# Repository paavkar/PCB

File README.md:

# PCB projects

## Introduction

This repository is meant for my PCB projects.

## IoT-Device

This is a PCB project where I am trying to design my own IoT device.
The MCU used in this is STM32U585VI with a ESP32-C3-WROOM-02 as a WiFi co-processor.
The design includes a reset-boot logic to choose the boot mode (i.e. either to
bootloader or flash). Included is also a port for SWD. In this board, USB-C is
used in 2.0 speed to give the board power and program the board.

### Schematic

You can take a look at the schematic in this repo from this
<a href="/IoT-Device/schematic.pdf">link.</a>

## Metro-M4-Express-Shield

This project is a much more simpler one as it is only a shield for the Metro M4 Express.
The goal of this PCB project was to design a shield that adds WiFi functionality
to the development board. The WiFi-module used is the ESP32-WROOM-32E, which is
used as a base for the FireBeetle board.

### Schematic

The schematic is available on this repo from the following
<a href="/Metro-M4-Express-Shield/schematics/schematic.pdf">link.</a>

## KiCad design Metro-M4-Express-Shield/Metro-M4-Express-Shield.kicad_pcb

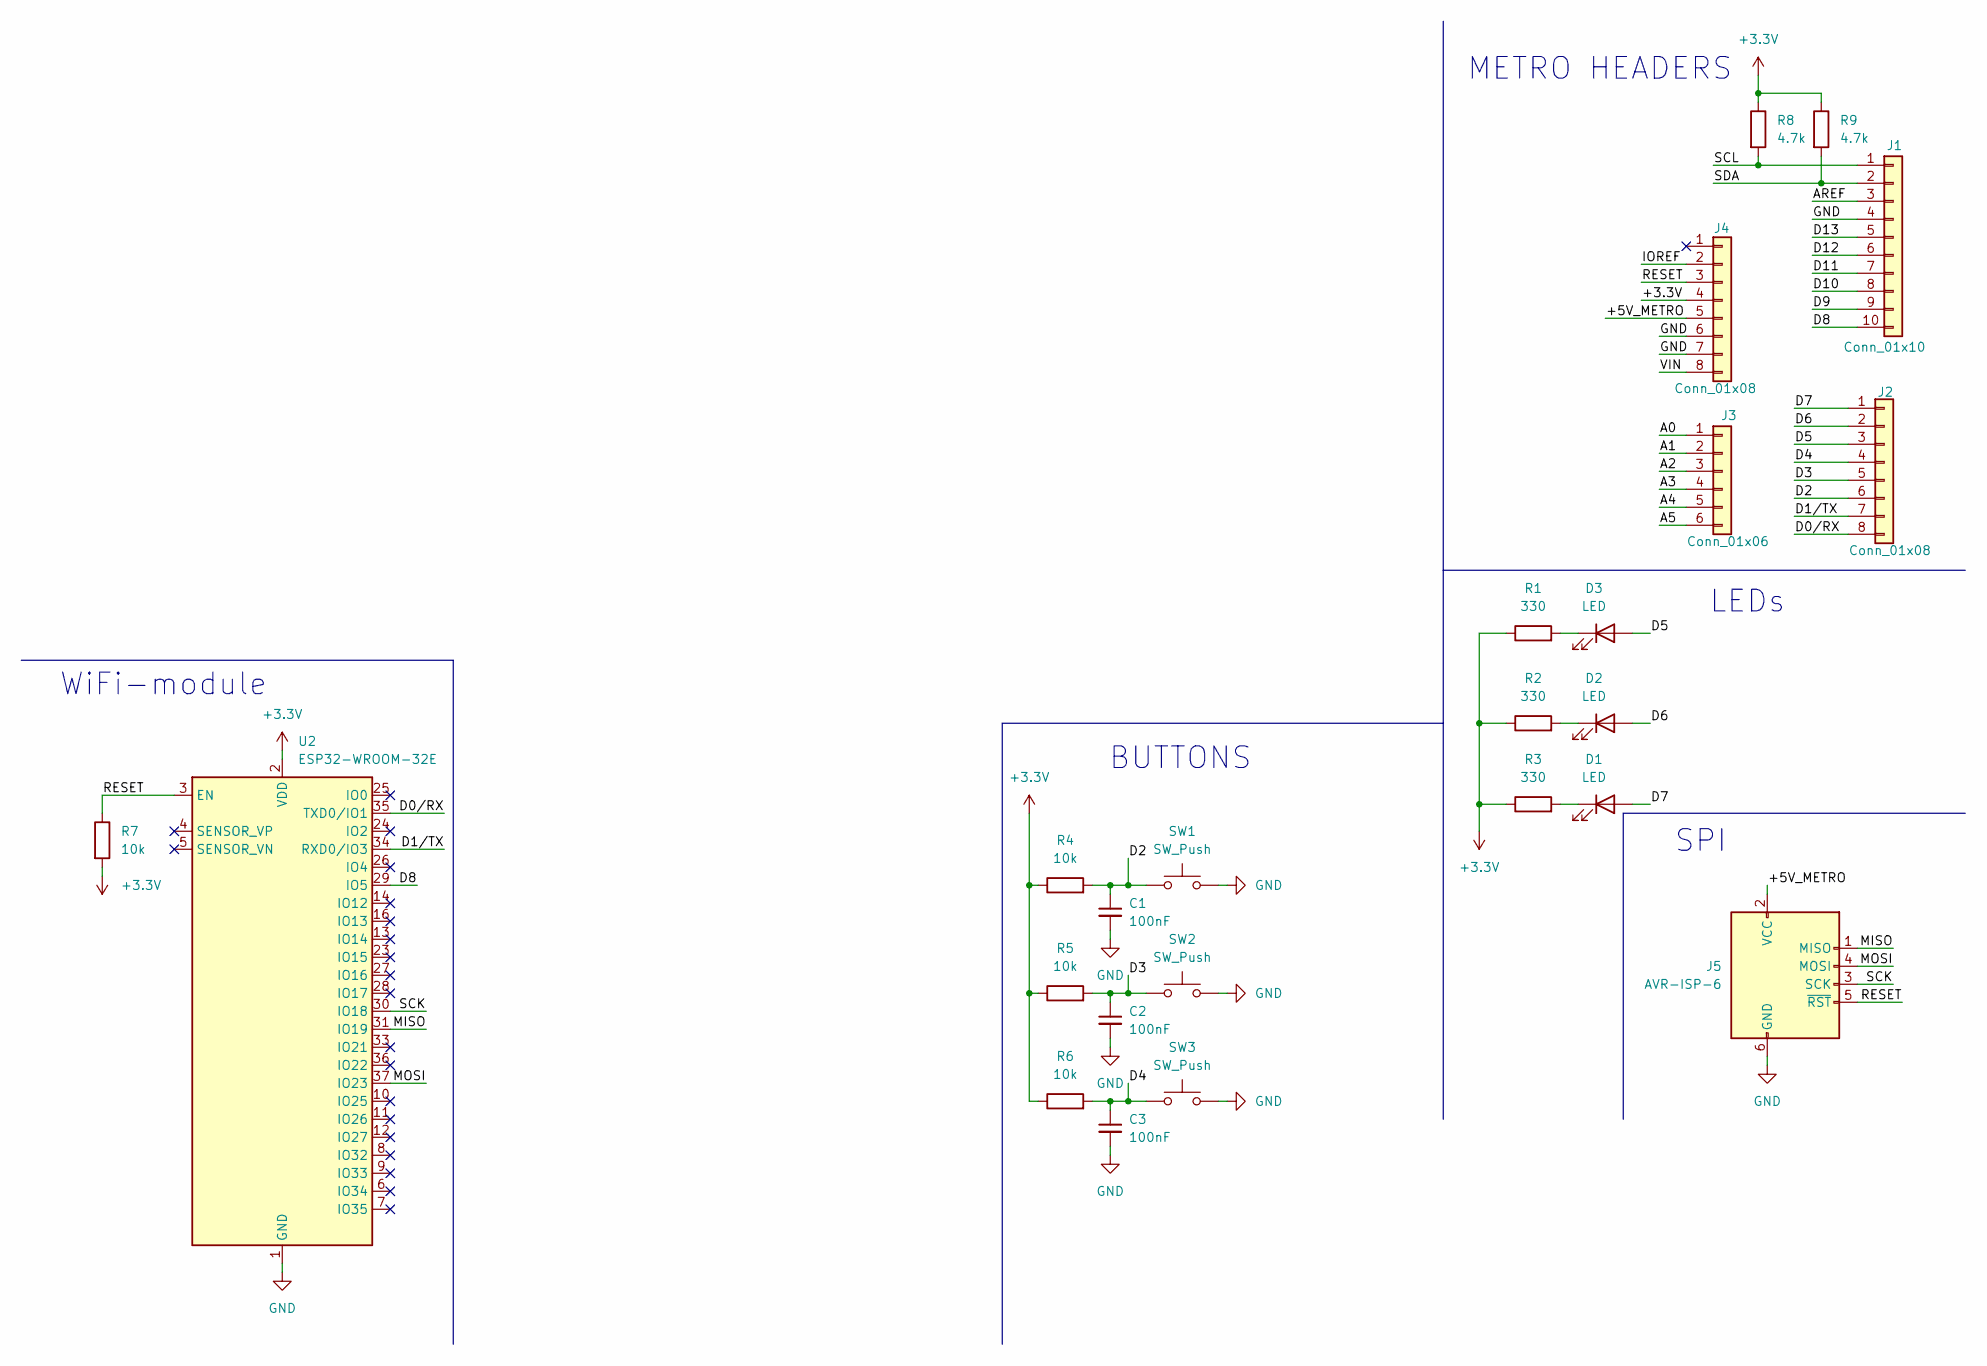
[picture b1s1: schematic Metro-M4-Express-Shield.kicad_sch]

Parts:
C1, C2, C3: 100nF; C_0603_1608Metric
D1, D2, D3: LED; LED_0603_1608Metric
J1: Conn_01x10; PinHeader_1x10_P2.54mm_Vertical
J2, J4: Conn_01x08; PinHeader_1x08_P2.54mm_Vertical
J3: Conn_01x06; PinHeader_1x06_P2.54mm_Vertical
J5: AVR-ISP-6; PinSocket_2x03_P2.54mm_Vertical
R1, R2, R3: 330; R_0603_1608Metric
R4, R5, R6, R7: 10k; R_0603_1608Metric
R8, R9: 4.7k; R_0603_1608Metric
SW1, SW2, SW3: SW_Push; SW_SPST_PTS647_Sx50
U2: ESP32-WROOM-32E; ESP32-WROOM-32D

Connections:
+3.3V: J4.4, R1.1, R2.1, R3.1, R4.1, R5.1, R6.1, R7.2, R8.1, R9.1, U2.2 (VDD)
/+5V_METRO: J4.5, J5.2 (VCC)
/A0: J3.1
/A1: J3.2
/A2: J3.3
/A3: J3.4
/A4: J3.5
/A5: J3.6
/AREF: J1.3
/D0/RX: J2.8, U2.35 (TXD0/IO1)
/D1/TX: J2.7, U2.34 (RXD0/IO3)
/D2: C1.1, J2.6, R4.2, SW1.1
/D3: C2.1, J2.5, R5.2, SW2.1
/D4: C3.1, J2.4, R6.2, SW3.1
/D5: D3.2 (A), J2.3
/D6: D2.2 (A), J2.2
/D7: D1.2 (A), J2.1
/D8: J1.10, U2.29 (IO5)
/D9: J1.9
/D10: J1.8
/D11: J1.7
/D12: J1.6
/D13: J1.5
/IOREF: J4.2
/MISO: J5.1 (MISO), U2.31 (IO19)
/MOSI: J5.4 (MOSI), U2.37 (IO23)
/RESET: J4.3, J5.5 (~RST), R7.1, U2.3 (EN)
/SCK: J5.3 (SCK), U2.30 (IO18)
/SCL: J1.1, R8.2
/SDA: J1.2, R9.2
/VIN: J4.8
GND: C1.2, C2.2, C3.2, J1.4, J4.6, J4.7, J5.6 (GND), SW1.2, SW2.2, SW3.2, U2.1 (GND), U2.15 (GND), U2.38 (GND), U2.39 (GND)
unnamed: D1.1 (K), R3.2
unnamed: D2.1 (K), R2.2
unnamed: D3.1 (K), R1.2

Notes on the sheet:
SPI
METRO HEADERS
WiFi-module
LEDs
BUTTONS

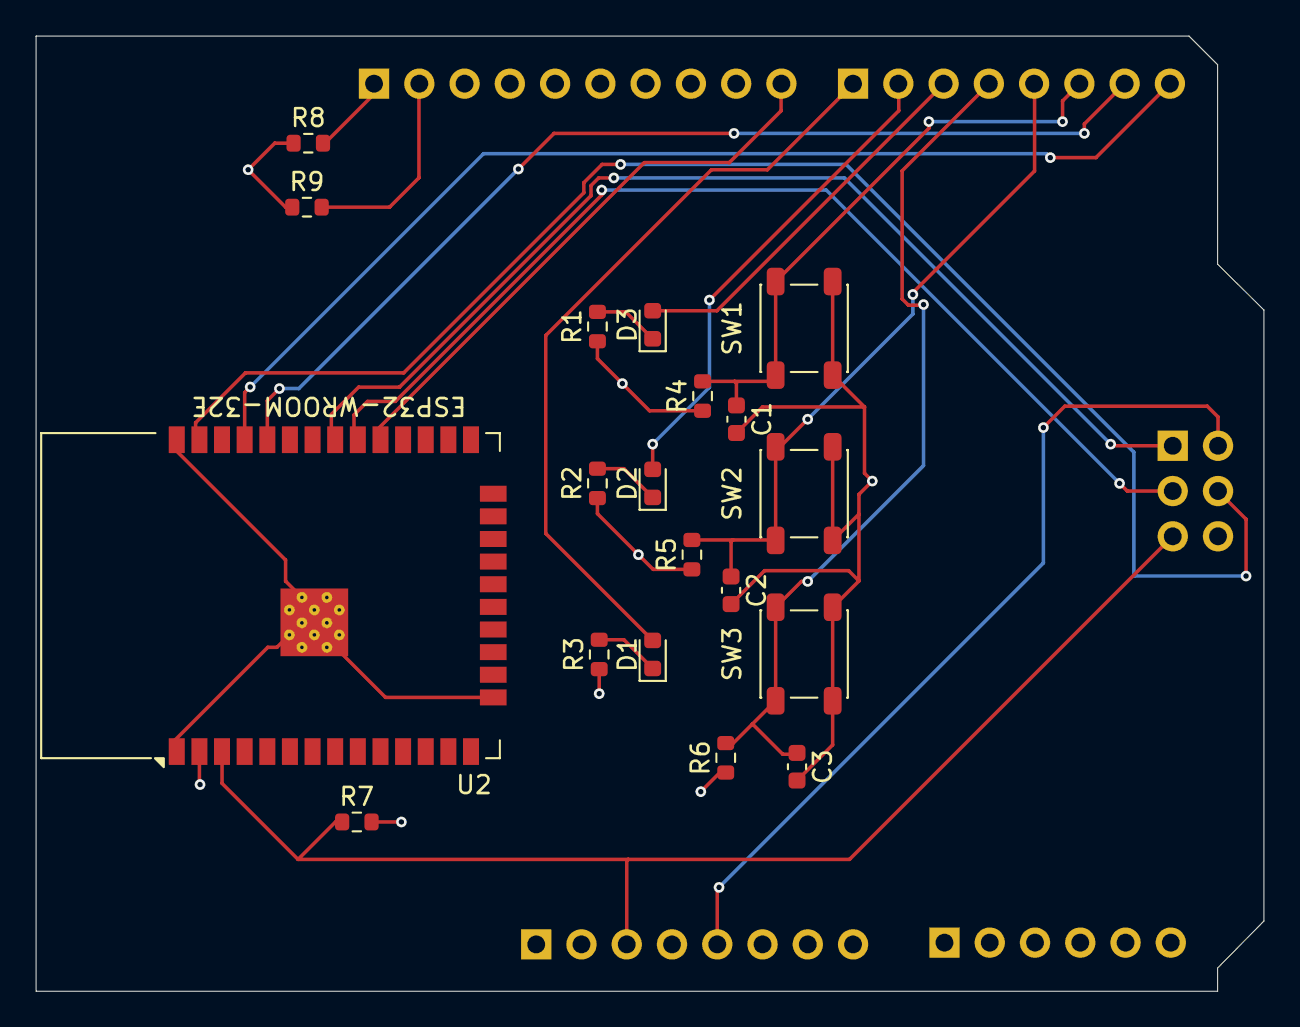
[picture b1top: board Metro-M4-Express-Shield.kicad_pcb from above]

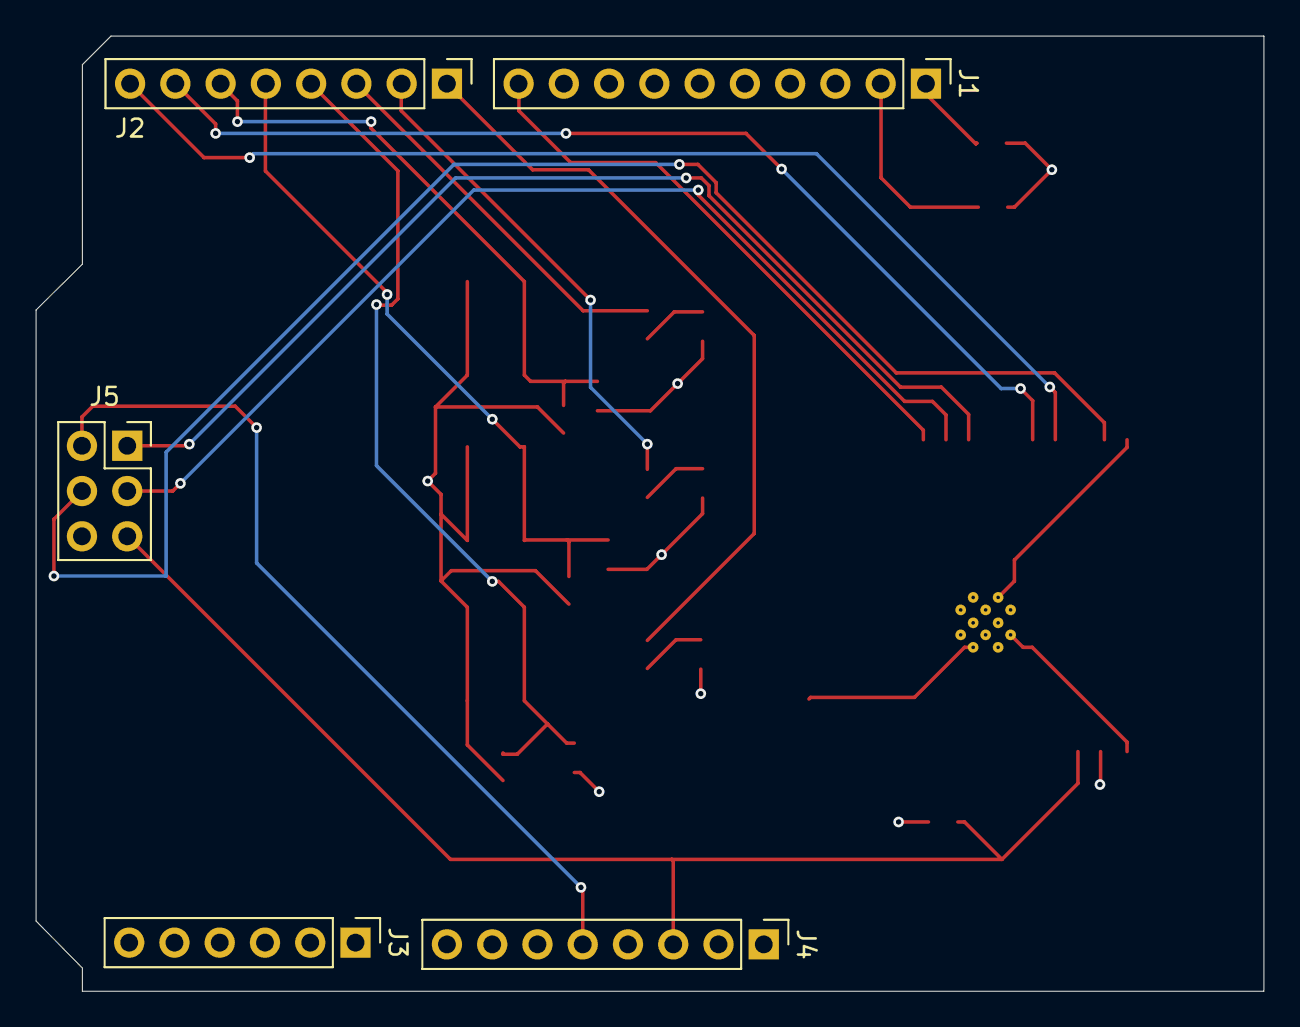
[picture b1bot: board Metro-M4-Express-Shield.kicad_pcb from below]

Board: 4 copper layers, 68.9 x 53.6 mm, 24 parts (5 on the bottom side), 21 nets.

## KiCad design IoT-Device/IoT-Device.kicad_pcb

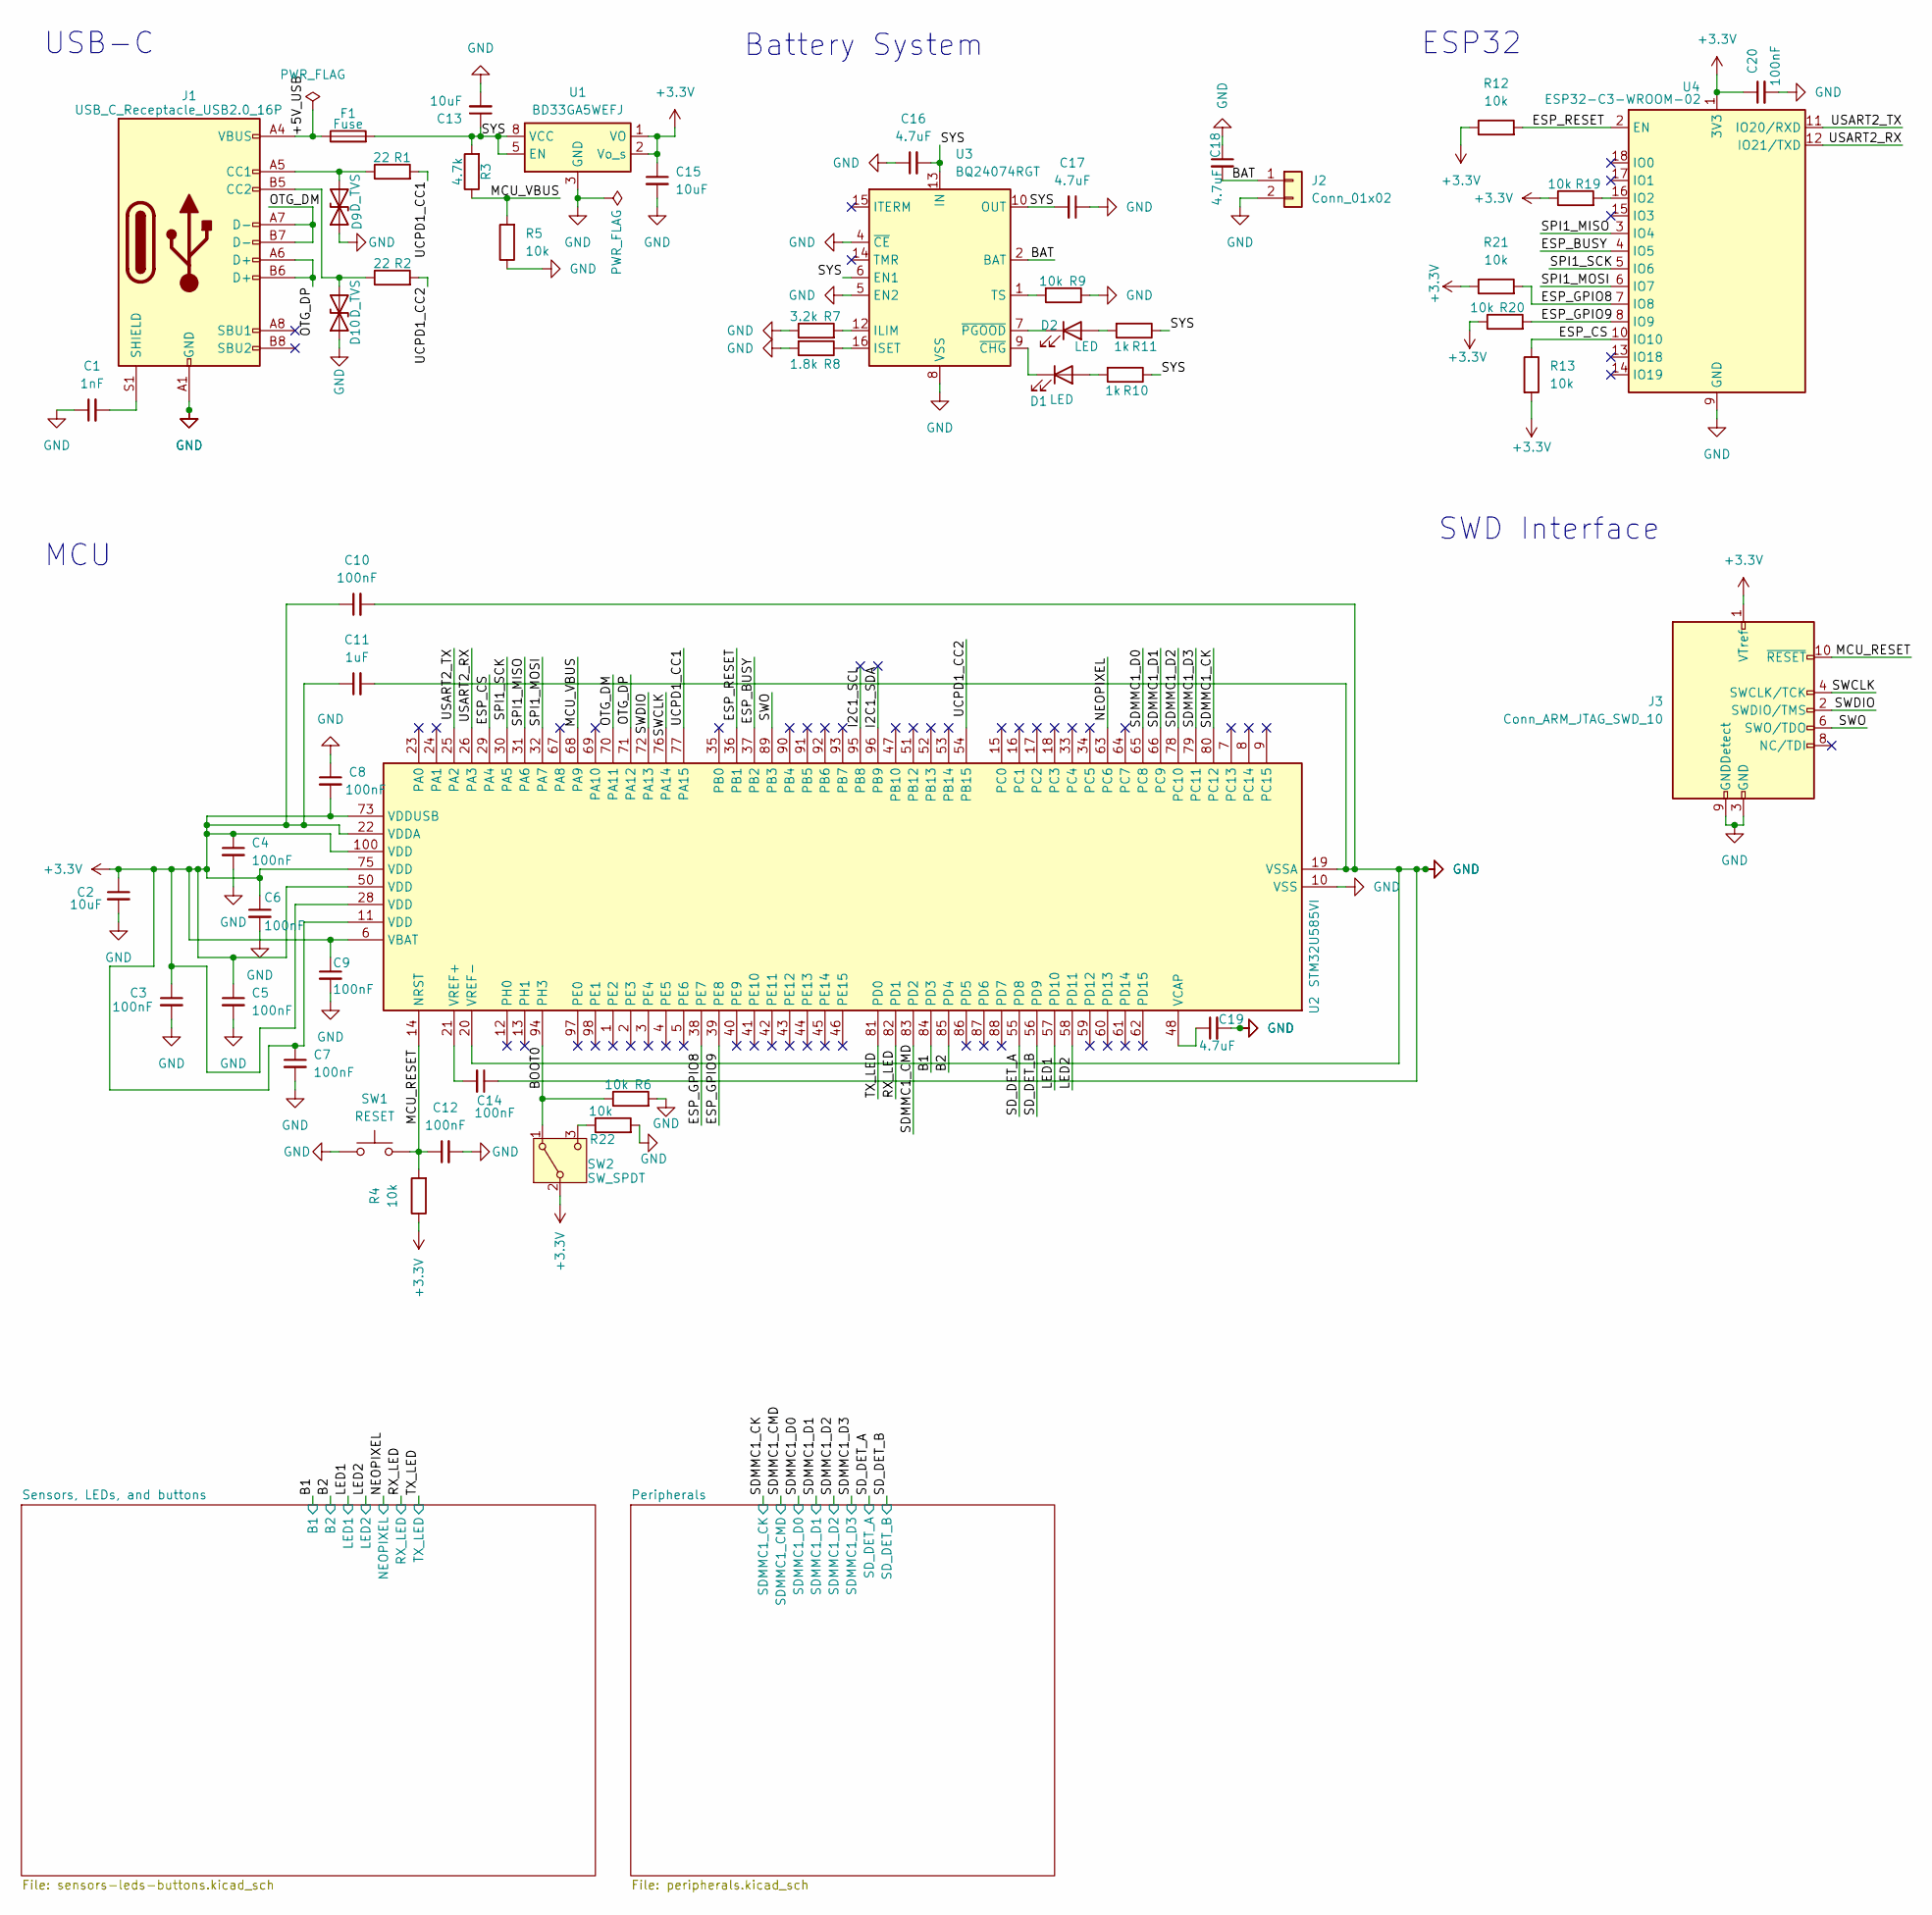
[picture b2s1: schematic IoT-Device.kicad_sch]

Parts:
C1: 1nF; C_0603_1608Metric
C2, C13, C15: 10uF; C_0603_1608Metric
C3, C4, C5, C6, C7, C8, C9, C10, C12, C14, C20: 100nF; C_0603_1608Metric
C11: 1uF; C_0603_1608Metric
C16, C17, C18, C19: 4.7uF; C_0603_1608Metric
D1, D2: LED; LED_0603_1608Metric
D9, D10: D_TVS; D_0603_1608Metric
F1: Fuse; Fuse_0603_1608Metric
J1: USB_C_Receptacle_USB2.0_16P; USB_C_Receptacle_GCT_USB4105-xx-A_16P_TopMnt_Horizontal
J2: Conn_01x02; JST_PH_B2B-PH-K_1x02_P2.00mm_Vertical
J3: Conn_ARM_JTAG_SWD_10; PinHeader_2x05_P1.27mm_Vertical_SMD
R1, R2: 22; R_0603_1608Metric
R3: 4.7k; R_0603_1608Metric
R4, R5, R6, R9, R12, R13, R19, R20, R21, R22: 10k; R_0603_1608Metric
R7: 3.2k; R_0603_1608Metric
R8: 1.8k; R_0603_1608Metric
R10, R11: 1k; R_0603_1608Metric
SW1: RESET; SW_SPST_PTS647_Sx50
SW2: SW_SPDT; SW_SPDT_PCM12
U1: BD33GA5WEFJ; HTSOP-8-1EP_3.9x4.9mm_P1.27mm_EP2.4x3.2mm
U2: STM32U585VI; LQFP-100_14x14mm_P0.5mm
U3: BQ24074RGT; VQFN-16-1EP_3x3mm_P0.5mm_EP1.6x1.6mm
U4: ESP32-C3-WROOM-02

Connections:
/+5V_USB: F1.1, J1.A4 (VBUS), J1.A9 (VBUS), J1.B4 (VBUS), J1.B9 (VBUS)
/B1: U2.84 (PD3); also elsewhere on the board
/B2: U2.85 (PD4); also elsewhere on the board
/BAT: C18.2, J2.1, U3.2 (BAT), U3.3 (BAT)
/BOOT0: R6.1, SW2.1 (A), U2.94 (PH3)
/ESP_BUSY: U2.37 (PB2), U4.4 (IO5)
/ESP_CS: R13.1, U2.29 (PA4), U4.10 (IO10)
/ESP_GPIO8: R21.2, U2.38 (PE7), U4.7 (IO8)
/ESP_GPIO9: R20.2, U2.39 (PE8), U4.8 (IO9)
/ESP_RESET: R12.2, U2.36 (PB1), U4.2 (EN)
/I2C1_SCL: U2.95 (PB8)
/I2C1_SDA: U2.96 (PB9)
/LED1: U2.57 (PD10); also elsewhere on the board
/LED2: U2.58 (PD11); also elsewhere on the board
/MCU_RESET: C12.1, J3.10 (~RESET), R4.2, SW1.2, U2.14 (NRST)
/MCU_VBUS: R3.1, R5.2, U2.68 (PA9)
/NEOPIXEL: U2.63 (PC6); also elsewhere on the board
/OTG_DM: J1.A7 (D-), J1.B7 (D-), U2.70 (PA11)
/OTG_DP: J1.A6 (D+), J1.B6 (D+), U2.71 (PA12)
/RX_LED: U2.82 (PD1); also elsewhere on the board
/SDMMC1_CK: U2.80 (PC12); also elsewhere on the board
/SDMMC1_CMD: U2.83 (PD2); also elsewhere on the board
/SDMMC1_D0: U2.65 (PC8); also elsewhere on the board
/SDMMC1_D1: U2.66 (PC9); also elsewhere on the board
/SDMMC1_D2: U2.78 (PC10); also elsewhere on the board
/SDMMC1_D3: U2.79 (PC11); also elsewhere on the board
/SD_DET_A: U2.55 (PD8); also elsewhere on the board
/SD_DET_B: U2.56 (PD9); also elsewhere on the board
/SPI1_MISO: U2.31 (PA6), U4.3 (IO4)
/SPI1_MOSI: U2.32 (PA7), U4.6 (IO7)
/SPI1_SCK: U2.30 (PA5), U4.5 (IO6)
/SWCLK: J3.4 (SWCLK/TCK), U2.76 (PA14)
/SWDIO: J3.2 (SWDIO/TMS), U2.72 (PA13)
/SWO: J3.6 (SWO/TDO), U2.89 (PB3)
/SYS: C13.1, C16.2, C17.2, F1.2, R3.2, R10.1, R11.1, U1.5 (EN), U1.8 (VCC), U3.6 (EN1), U3.10 (OUT), U3.11 (OUT), U3.13 (IN)
/TX_LED: U2.81 (PD0); also elsewhere on the board
/UCPD1_CC1: R1.2, U2.77 (PA15)
/UCPD1_CC2: R2.2, U2.54 (PB15)
/USART2_RX: U2.26 (PA3), U4.12 (IO21/TXD)
/USART2_TX: U2.25 (PA2), U4.11 (IO20/RXD)
unnamed: D1.2 (A), R10.2
unnamed: D1.1 (K), U3.9 (~CHG)
unnamed: D2.2 (A), R11.2
unnamed: D2.1 (K), U3.7 (~PGOOD)
unnamed: D9.2 (A2), J1.A5 (CC1), R1.1
unnamed: D10.2 (A2), J1.B5 (CC2), R2.1
unnamed: C1.2, J1.S1 (SHIELD)
unnamed: R22.1, SW2.3 (C)
unnamed: C19.1, U2.48 (VCAP)
unnamed: C14.2, U2.21 (VREF+)
unnamed: R7.2, U3.12 (ILIM)
unnamed: R8.1, U3.16 (ISET)
unnamed: R9.2, U3.1 (TS)
unnamed: R19.2, U4.16 (IO2)

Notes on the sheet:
SWD Interface
Battery System
MCU
ESP32
USB-C

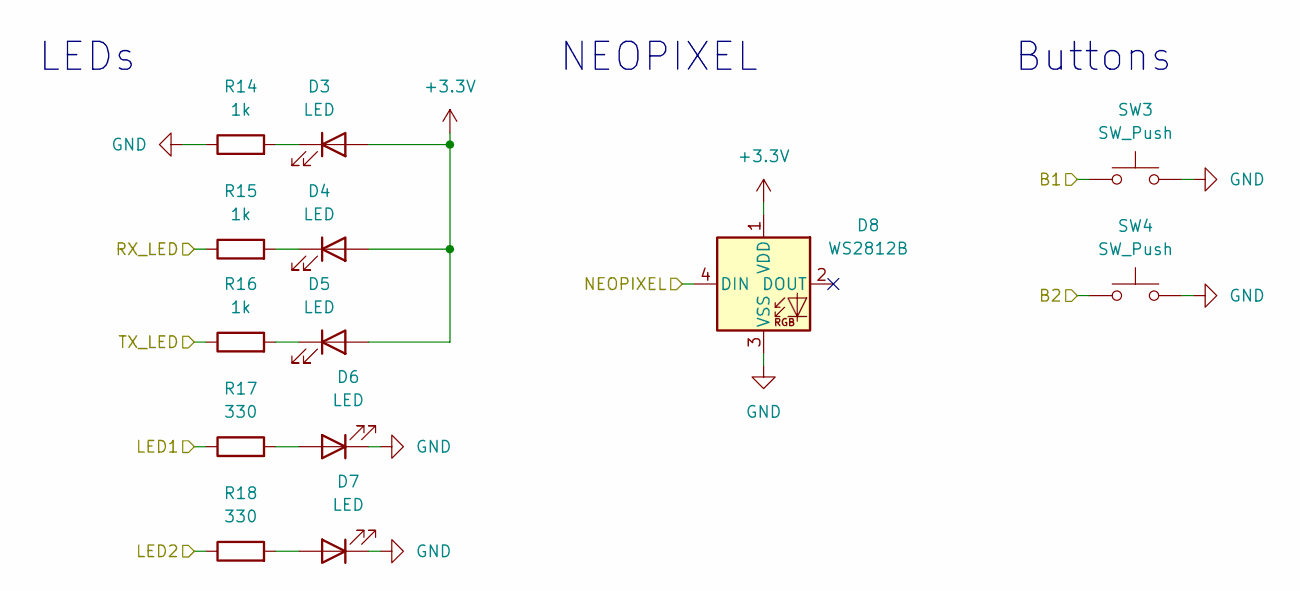
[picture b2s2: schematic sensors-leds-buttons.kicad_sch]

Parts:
D3, D4, D5, D6, D7: LED; LED_0603_1608Metric
D8: WS2812B; LED_WS2812B_PLCC4_5.0x5.0mm_P3.2mm
R14, R15, R16: 1k; R_0603_1608Metric
R17, R18: 330; R_0603_1608Metric
SW3, SW4: SW_Push; SW_SPST_PTS647_Sx50

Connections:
/B1: SW3.1; also elsewhere on the board
/B2: SW4.1; also elsewhere on the board
/LED1: R17.1; also elsewhere on the board
/LED2: R18.1; also elsewhere on the board
/NEOPIXEL: D8.4 (DIN); also elsewhere on the board
/RX_LED: R15.1; also elsewhere on the board
/TX_LED: R16.1; also elsewhere on the board
unnamed: D3.1 (K), R14.2
unnamed: D4.1 (K), R15.2
unnamed: D5.1 (K), R16.2
unnamed: D6.2 (A), R17.2
unnamed: D7.2 (A), R18.2

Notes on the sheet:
NEOPIXEL
LEDs
Buttons

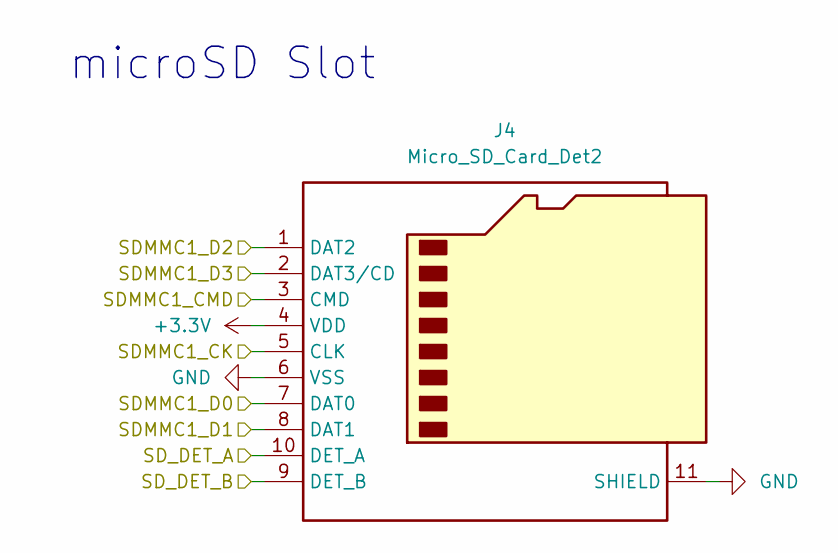
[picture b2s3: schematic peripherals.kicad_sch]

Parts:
J4: Micro_SD_Card_Det2; microSD_HC_Hirose_DM3BT-DSF-PEJS

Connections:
/SDMMC1_CK: J4.5 (CLK); also elsewhere on the board
/SDMMC1_CMD: J4.3 (CMD); also elsewhere on the board
/SDMMC1_D0: J4.7 (DAT0); also elsewhere on the board
/SDMMC1_D1: J4.8 (DAT1); also elsewhere on the board
/SDMMC1_D2: J4.1 (DAT2); also elsewhere on the board
/SDMMC1_D3: J4.2 (DAT3/CD); also elsewhere on the board
/SD_DET_A: J4.10 (DET_A); also elsewhere on the board
/SD_DET_B: J4.9 (DET_B); also elsewhere on the board

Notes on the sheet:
microSD Slot

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
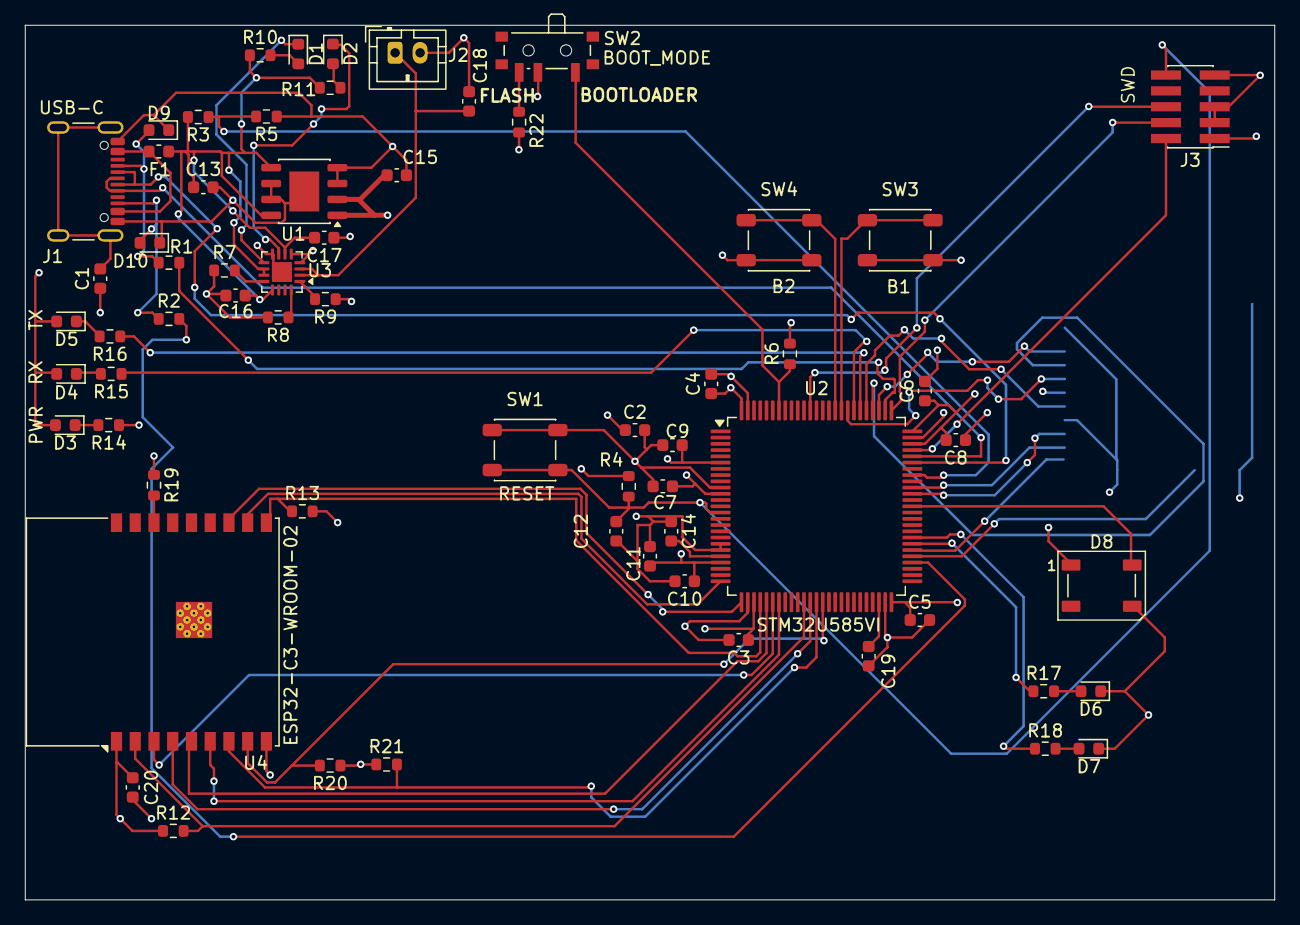
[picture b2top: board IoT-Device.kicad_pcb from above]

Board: 4 copper layers, 100.0 x 70.0 mm, 65 parts (1 on the bottom side), 59 nets.

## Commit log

2026-02-24 PCB projects repository
2026-02-25 add schematics, update metro shield
2026-02-25 add README, update IoT-device schematic
2026-02-25 Fix schematic link in README
2026-02-25 update IoT-device schematic, update pcb to free space around more pins
2026-02-26 add battery power to design
2026-02-26 add title to battery system section
2026-02-26 fix ESP32 (GPIO2 & GPIO9) issue on schematic
2026-02-26 update schematic and PCB to allow ESP32-C3 boot mode change via STM32
2026-02-26 change two ESP32 pins for slightly more appropriate ones on STM32 (ESP_BUSY->PB2 (SPI1_RDY)
2026-02-27 update SW2 GND routing
2026-02-27 connect USB-C port's CC1 and CC2 to STM32's CC1 and CC2 pins
2026-02-28 add microSD card slot
2026-03-01 fix STM32<->ESP32-C3 UART communication, update labels on shcematics
2026-05-19 fix ESP32 RX/TX connection
